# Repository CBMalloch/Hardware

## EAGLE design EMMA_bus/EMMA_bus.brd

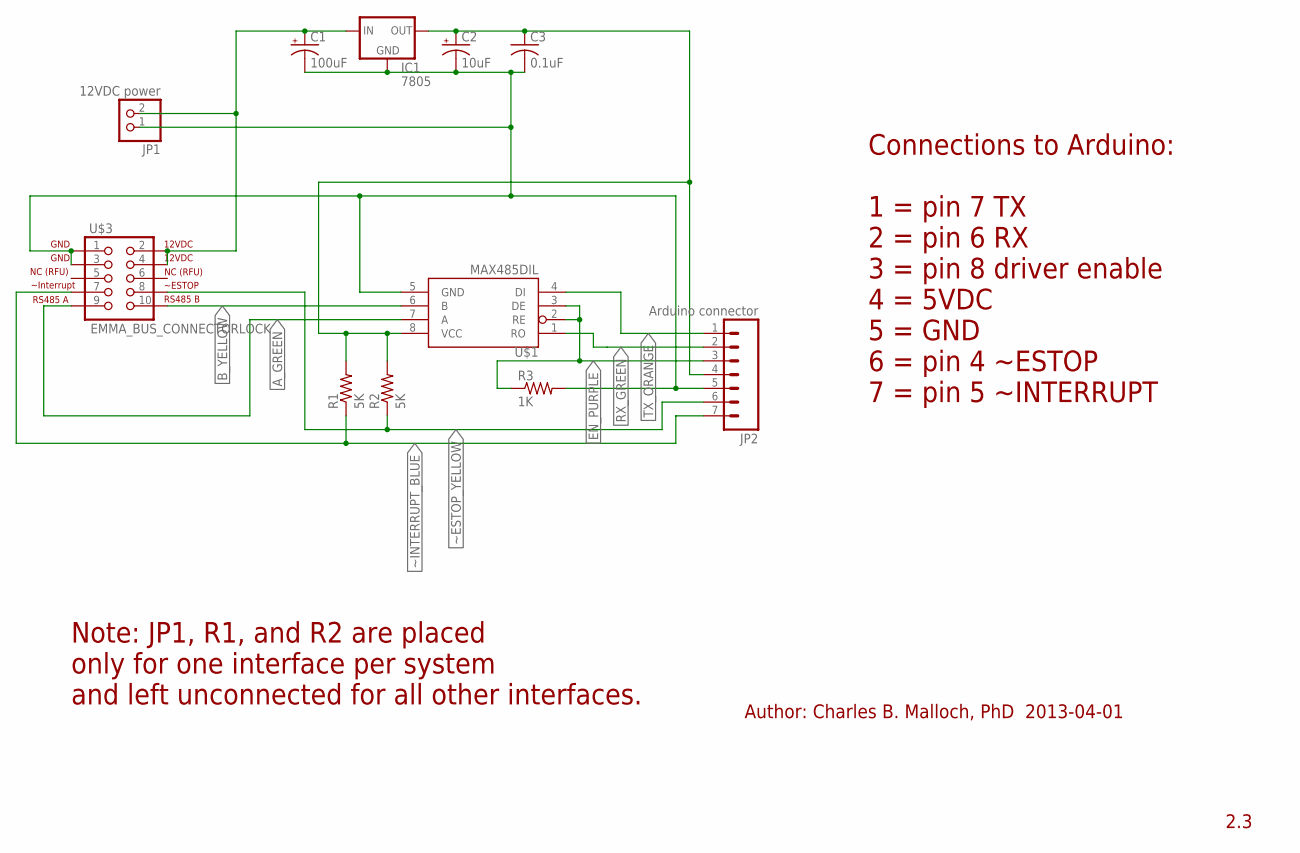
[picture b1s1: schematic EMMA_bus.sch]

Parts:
C1: 100uF; TT2D7
C2: 10uF; E1,8-4
C3: 0.1uF; C025-025X050
IC1: 7805; TO-220-ALT
JP1: 12VDC power; 1X02
JP2: Arduino connector; 1X07_LOCK_LONGPADS
R1, R2: 5K; 0309/12
R3: 1K; 0207/5V
U$1: MAX485DIL; DIL08
U$3: EMMA_BUS_CONNECTORLOCK; 2X5-SHROUDED_LOCK

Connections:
A_GREEN: U$1.7 (A), U$3.9
B_YELLOW: U$1.6 (B), U$3.10
EN_PURPLE: JP2.3, R3.1, U$1.2 (RE), U$1.3 (DE)
GND: C1.-, C2.-, C3.2, IC1.GND, JP1.1, JP2.5, R3.2, U$1.5 (GND), U$3.1, U$3.3
PWR: C2.+, C3.1, IC1.OUT, JP2.4, R1.2, R2.2, U$1.8 (VCC)
RX_GREEN: JP2.2, U$1.1 (RO)
TX_ORANGE: JP2.1, U$1.4 (DI)
VIN: C1.+, IC1.IN, JP1.2, U$3.2, U$3.4
~ESTOP_YELLOW: JP2.6, R2.1, U$3.8
~INTERRUPT_BLUE: JP2.7, R1.1, U$3.7

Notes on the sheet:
Author: Charles B. Malloch, PhD 2013-04-01
2.3
Connections to Arduino: 1 = pin 7 TX 2 = pin 6 RX 3 = pin 8 driver enable 4 = 5VDC 5 = GND 6 = pin 4 ~ESTOP 7 = pin 5 ~INTERRUPT
Note: JP1, R1, and R2 are placed only for one interface per system and left unconnected for all other interfaces.

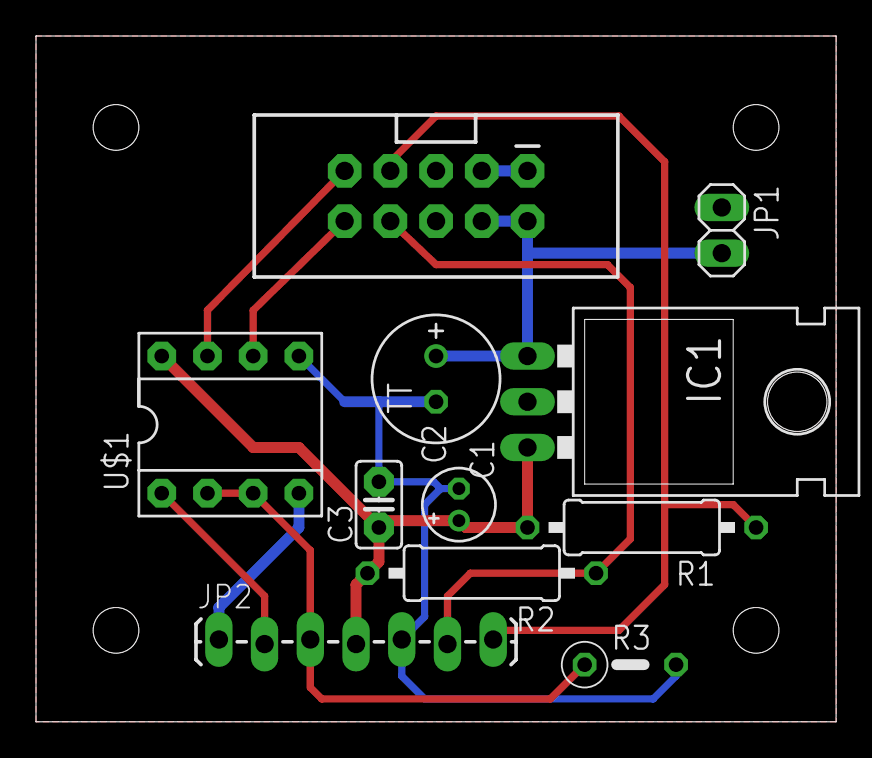
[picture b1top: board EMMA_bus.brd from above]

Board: 2 copper layers, 44.5 x 38.1 mm, 11 parts (0 on the bottom side), 10 nets.

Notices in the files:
parts and their libraries:
SparkFun-DigitalIC: Licensing: CC v3.0 Share-Alike You are welcome to use this library for commercial purposes.
